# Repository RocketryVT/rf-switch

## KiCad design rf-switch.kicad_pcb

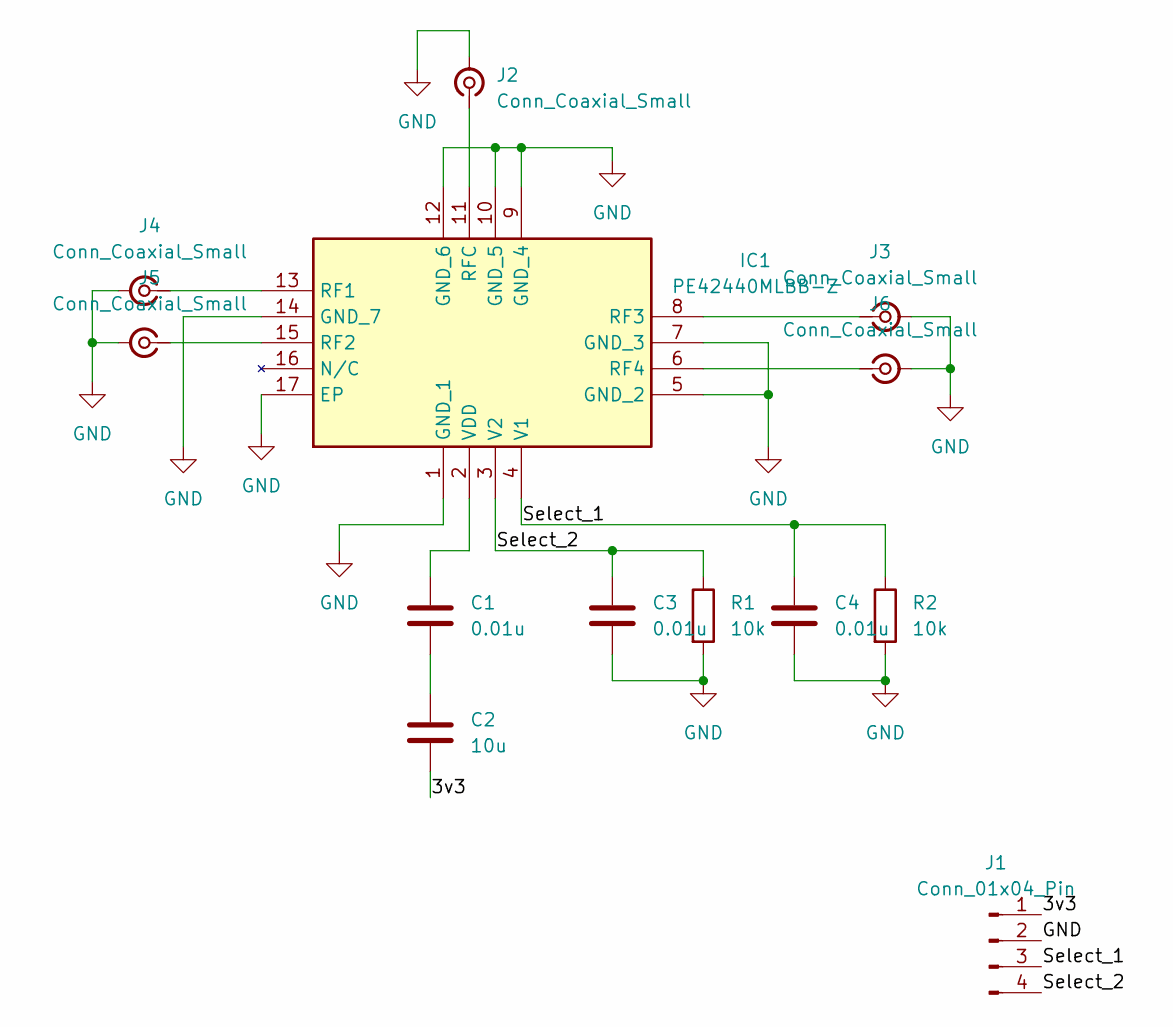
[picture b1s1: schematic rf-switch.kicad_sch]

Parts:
C1, C3, C4: 0.01u; C_1206_3216Metric
C2: 10u; C_1206_3216Metric
IC1: PE42440MLBB-Z; PE42440; Mouser Part Number 81-PE42440MLBB-Z
J1: Conn_01x04_Pin; PinHeader_1x04_P2.54mm_Vertical
J2, J3, J4, J5, J6: Conn_Coaxial_Small; SMA_Amphenol_132289_EdgeMount
R1, R2: 10k; R_1206_3216Metric

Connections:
/3v3: C2.2, J1.1
/Select_1: C4.1, IC1.4 (V1), J1.3, R2.1
/Select_2: C3.1, IC1.3 (V2), J1.4, R1.1
GND: C3.2, C4.2, IC1.1 (GND_1), IC1.5 (GND_2), IC1.7 (GND_3), IC1.9 (GND_4), IC1.10 (GND_5), IC1.12 (GND_6), IC1.14 (GND_7), IC1.17 (EP), J1.2, J2.2 (Ext), J3.2 (Ext), J4.2 (Ext), J5.2 (Ext), J6.2 (Ext), R1.2, R2.2
unnamed: C1.2, C2.1
unnamed: IC1.13 (RF1), J4.1 (In)
unnamed: IC1.15 (RF2), J5.1 (In)
unnamed: IC1.8 (RF3), J3.1 (In)
unnamed: IC1.6 (RF4), J6.1 (In)
unnamed: IC1.11 (RFC), J2.1 (In)
unnamed: C1.1, IC1.2 (VDD)

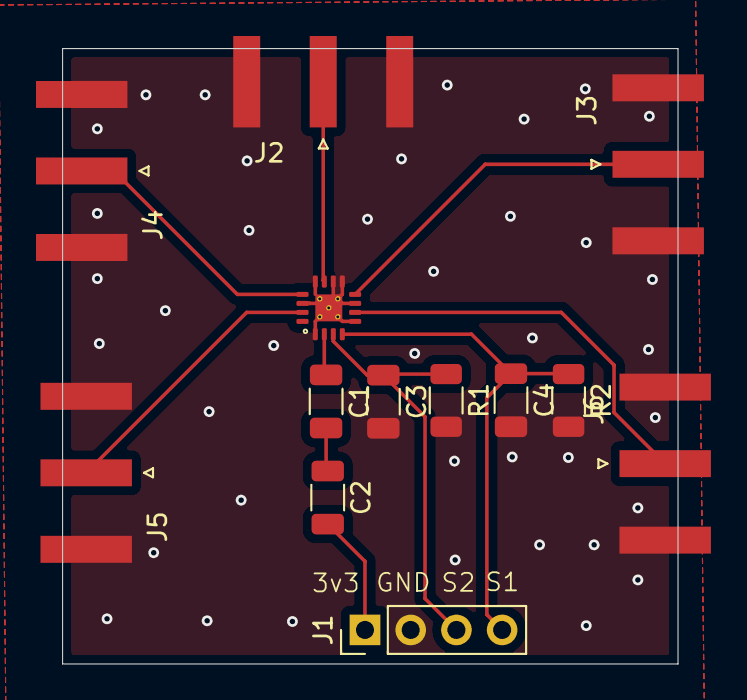
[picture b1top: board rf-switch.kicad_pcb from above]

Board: 2 copper layers, 34.2 x 34.2 mm, 13 parts (0 on the bottom side), 11 nets.

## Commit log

2025-02-02 First commit, project created
2025-03-02 Symbol & Footprint Created for SP4T RF Switch
2025-03-30 Schematic w/ footprints done
    Need to do PCB layout
2025-03-30 Started PCB Layout
2025-04-06 Semi-completed PCB Schematic
    Done wiring some of the components. Still need to finish this.
2025-04-13 PCB layout is done
